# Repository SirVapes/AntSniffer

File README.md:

# AntSniffer
This device is used to tap into the signals on an Antminer data cable for logic analyzers and other development purposes.
The base design is a 2 layer PCB, with 2 SMD connectors that are compatible with Antminer 18 pin data cables. 
These cables are used for plugging in the hashboard to the control board.
All data connections are broken out into a pin header with labels for their functions. Also included are two switches.
These switches reset the control board, and reset the plug state of the miner. 

For other cool stuff like this join my Discord! There we discuss, design, and develop open source mining solutions and a little of everything else too!
https://discord.gg/Px8RAvb9nr

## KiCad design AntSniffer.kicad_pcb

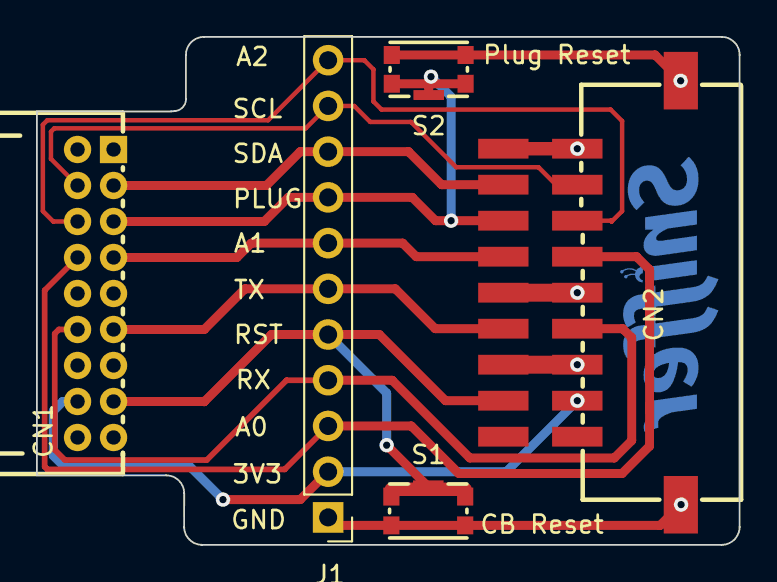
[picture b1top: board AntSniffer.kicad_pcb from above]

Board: 2 copper layers, 39.0 x 28.2 mm, 5 parts (0 on the bottom side), 11 nets.

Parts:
CN1: X2026WRS-2X09D-LPSW; CONN-TH_X2026WR-2-09-N0SN
CN2: X2026WRS-2X09D-LPSW; CONN-SMD_X2026WRS-2X09D-LPSW
J1: Conn_01x11_Pin; PinHeader_1x11_P2.54mm_Vertical
S1, S2: 435441019830

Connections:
/3V3: CN1.16, CN2.3, J1.2
/A0: CN1.8, CN2.11, J1.3
/A1: CN1.7, CN2.12, J1.7
/A2: CN1.6, CN2.13, J1.11
/PLUG: CN1.5, CN2.14, J1.8, S2.1, S2.4, S2.GND
/RST: CN1.15, CN2.4, J1.5, S1.1, S1.4, S1.GND
/RX: CN1.12, CN2.7, J1.4
/SCL: CN1.4, CN2.15, J1.10
/SDA: CN1.3, CN2.16, J1.9
/TX: CN1.11, CN2.8, J1.6
GND: CN1.1, CN1.2, CN1.9, CN1.10, CN1.13, CN1.14, CN2.5, CN2.6, CN2.9, CN2.10, CN2.17, CN2.18, CN2.19, CN2.20, J1.1, S1.2, S1.3, S2.2, S2.3

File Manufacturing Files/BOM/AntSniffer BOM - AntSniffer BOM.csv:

Component Count:,4,,,,,,,
Item,Qty,Reference(s),Value,LibPart,Footprint,Datasheet,DNP,LCSC Part
1,2,"CN1, CN2",X2026WRS-2X09D-LPSW,x2026:X2026WRS-2X09D-LPSW,EASYEDA2KICAD:CONN-SMD_X2026WRS-2X09D-LPSW,https://datasheet.lcsc.com/lcsc/2110111530_XKB-Connectivity-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,,C718164
2,2,"S1, S2",435441019830,,435441019830,https://www.mouser.com/ProductDetail/Wurth-Elektronik/435441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,,
3,1,J1,Conn_01x10_MountingPin,Connector_Generic_MountingPin:Conn_01x10_MountingPin,Connector_PinHeader_2.54mm:PinHeader_1x10_P2.54mm_Vertical,https://datasheet.lcsc.com/lcsc/2307210925_XKB-Connectivity-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,,C706882

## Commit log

2023-12-17 Release V2.1
2024-03-21 Initial Upload
